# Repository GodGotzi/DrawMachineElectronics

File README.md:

# DrawMachineElectronics
DrawMachineElectronics

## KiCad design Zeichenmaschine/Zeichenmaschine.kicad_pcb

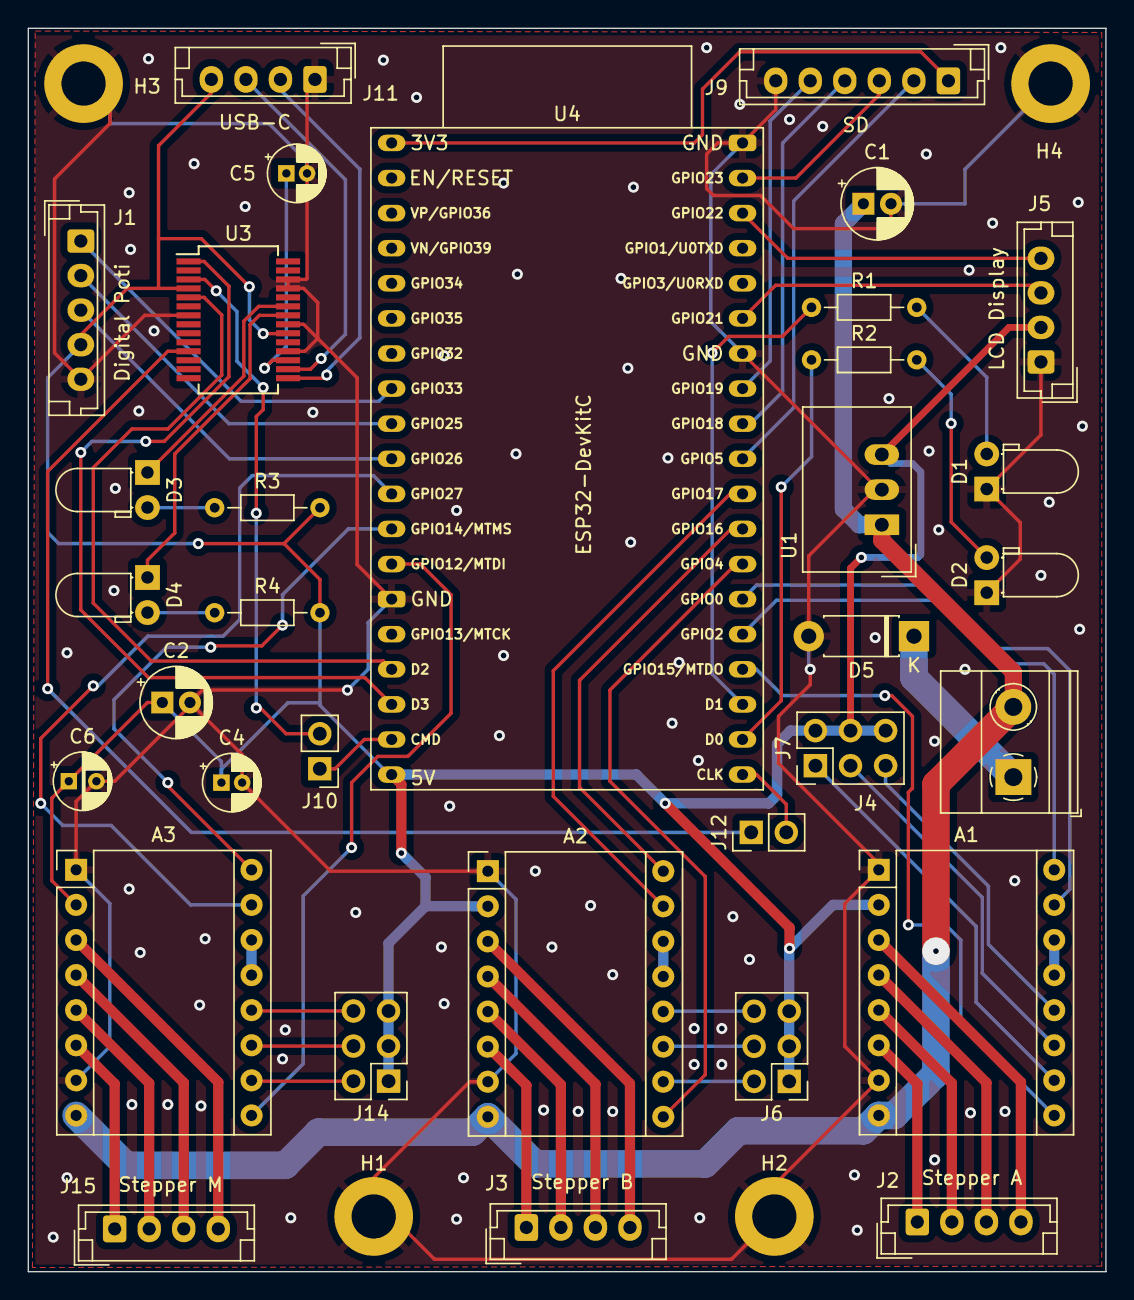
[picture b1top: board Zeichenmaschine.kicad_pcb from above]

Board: 2 copper layers, 78.0 x 90.0 mm, 37 parts (0 on the bottom side), 64 nets.

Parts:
A1: Stepper_1_A4988; Pololu_Breakout-16_15.2x20.3mm
A2: Stepper_2_A4988; Pololu_Breakout-16_15.2x20.3mm
A3: Stepper_3_A4988; Pololu_Breakout-16_15.2x20.3mm
C1, C2: C_Polarized; CP_Radial_D5.0mm_P2.00mm
C4, C5: 0.1µF; CP_Radial_D4.0mm_P1.50mm
C6: 10µF; CP_Radial_D4.0mm_P2.00mm
D1, D2: RED; LED_D3.0mm_Horizontal_O1.27mm_Z2.0mm
D3: RED_USB; LED_D3.0mm_Horizontal_O1.27mm_Z2.0mm
D4: GREEN_USB; LED_D3.0mm_Horizontal_O1.27mm_Z2.0mm
D5: D_Schottky; D_DO-41_SOD81_P7.62mm_Horizontal
H1, H2, H3, H4: MountingHole_Pad; MountingHole_3.2mm_M3_ISO7380_Pad
J1: interface; JST_EH_B5B-EH-A_1x05_P2.50mm_Vertical
J2: Stepper_1; JST_EH_B4B-EH-A_1x04_P2.50mm_Vertical
J3: Stepper_2; JST_EH_B4B-EH-A_1x04_P2.50mm_Vertical
J4: Screw_Terminal_01x02; TerminalBlock_Phoenix_MKDS-1,5-2-5.08_1x02_P5.08mm_Horizont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
J5: Display; JST_EH_B4B-EH-A_1x04_P2.50mm_Vertical
J6: Stepper_2_JUMPER; PinHeader_2x03_P2.54mm_Vertical
J7: Stepper_1_JUMPER; PinHeader_2x03_P2.54mm_Vertical
J9: SD_SPI; JST_EH_B6B-EH-A_1x06_P2.50mm_Vertical
J10, J12: Conn_01x02_Male; PinHeader_1x02_P2.54mm_Vertical
J11: USB_C; JST_EH_B4B-EH-A_1x04_P2.50mm_Vertical
J14: Stepper_3_JUMPER; PinHeader_2x03_P2.54mm_Vertical
J15: Stepper_3; JST_EH_B4B-EH-A_1x04_P2.50mm_Vertical
R1, R2: 270; R_Axial_DIN0204_L3.6mm_D1.6mm_P7.62mm_Horizontal
R3, R4: 1k; R_Axial_DIN0204_L3.6mm_D1.6mm_P7.62mm_Horizontal
U1: TSR_1-2450; Converter_DCDC_TRACO_TSR-1_THT
U3: FT232RL; SSOP-28_5.3x10.2mm_P0.65mm
U4: ESP32-DevKitC

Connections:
+3V3: J9.1, U4.1 (3V3)
+5V: A1.2 (VDD), A2.2 (VDD), A3.2 (VDD), C2.1, C4.1, C6.1, J1.4, J5.2, J6.1, J6.3, J6.5, J7.2, J7.4, J7.6, J11.4, J14.1, J14.3, J14.5, R3.2, R4.2, U1.3 (Vout), U3.4 (VCCIO), U3.20 (VCC), U4.19 (5V)
+12V: A1.8 (VMOT), A2.8 (VMOT), A3.8 (VMOT), C1.1, J4.2, U1.1 (Vin)
/CLK: J9.4, U4.30 (GPIO18)
/CS: J9.2, U4.29 (*GPIO5)
/CTS: J12.1, U3.11 (CTS)
/LED1: R1.1, U4.22 (SD_DATA1/GPIO8)
/LED2: R2.1, U4.21 (SD_DATA0/GPIO7)
/MISO: J9.5, U4.31 (GPIO19)
/MOSI: J9.3, U4.37 (GPIO23)
/RTS: J10.2, U3.3 (RTS)
/RX: U3.5 (RXD), U4.16 (SD_DATA2/GPIO9)
/Stepper_1_DIR: A3.16 (DIR), U4.12 (MTMS/GPIO14/ADC2_CH6)
/Stepper_1_STEP: A3.15 (STEP), U4.11 (ADC2_CH7/GPIO27)
/Stepper_2_DIR: A2.16 (DIR), U4.27 (GPIO16)
/Stepper_2_STEP: A2.15 (STEP), U4.28 (GPIO17)
/TX: U3.1 (TXD), U4.17 (SD_DATA3/GPIO10)
/display_SCL: J5.4, U4.36 (GPIO22)
/display_SDA: J5.3, U4.33 (GPIO21)
/enable_Stepper_1: A3.9 (~ENABLE), U4.13 (*MTDI/GPIO12/ADC2_CH5)
/enable_Stepper_2: A2.9 (~ENABLE), U4.26 (ADC2_CH0/GPIO4)
/enable_stepper_gear_motor: A1.9 (~ENABLE), U4.23 (*MTDO/GPIO15/ADC2_CH3)
/interface_CLK: J1.1, U4.8 (32K_XN/GPIO33/ADC1_CH5)
/interface_DT: J1.2, U4.9 (DAC_1/ADC2_CH8/GPIO25)
/interface_SW: J1.3, U4.10 (DAC_2/ADC2_CH9/GPIO26)
/stepper_gear_motor_1A: A1.15 (STEP), U4.25 (*GPIO0/BOOT/ADC2_CH1)
/stepper_gear_motor_2A: A1.16 (DIR), U4.24 (ADC2_CH2/*GPIO2)
GND: A1.1 (GND), A1.7 (GND), A2.1 (GND), A2.7 (GND), A3.1 (GND), A3.7 (GND), C1.2, C2.2, C4.2, C5.2, C6.2, D1.1 (K), D2.1 (K), D5.2 (A), H1.1, H2.1, H3.1, H4.1, J1.5, J5.1, J9.6, J11.1, U1.2 (GND), U3.7 (GND), U3.18 (GND), U3.21 (GND), U3.25 (AGND), U3.26 (TEST), U4.14 (GND), U4.32 (GND), U4.38 (GND)
unnamed: A1.3 (1B), J2.4
unnamed: A1.4 (1A), J2.3
unnamed: A1.5 (2A), J2.2
unnamed: A1.6 (2B), J2.1
unnamed: A1.10 (MS1), J7.1
unnamed: A1.11 (MS2), J7.3
unnamed: A1.12 (MS3), J7.5
unnamed: A1.13 (~RESET), A1.14 (~SLEEP)
unnamed: A2.3 (1B), J3.4
unnamed: A2.4 (1A), J3.3
unnamed: A2.5 (2A), J3.2
unnamed: A2.6 (2B), J3.1
unnamed: A2.10 (MS1), J6.2
unnamed: A2.11 (MS2), J6.4
unnamed: A2.12 (MS3), J6.6
unnamed: A2.13 (~RESET), A2.14 (~SLEEP)
unnamed: A3.3 (1B), J15.4
unnamed: A3.4 (1A), J15.3
unnamed: A3.5 (2A), J15.2
unnamed: A3.6 (2B), J15.1
unnamed: A3.10 (MS1), J14.2
unnamed: A3.11 (MS2), J14.4
unnamed: A3.12 (MS3), J14.6
unnamed: A3.13 (~RESET), A3.14 (~SLEEP)
unnamed: C5.1, U3.17 (3V3OUT)
unnamed: D1.2 (A), R1.2
unnamed: D2.2 (A), R2.2
unnamed: D3.1 (K), U3.23 (CBUS0)
unnamed: D3.2 (A), R3.1
unnamed: D4.1 (K), U3.22 (CBUS1)
unnamed: D4.2 (A), R4.1
unnamed: D5.1 (K), J4.1
unnamed: J10.1, U4.18 (CMD)
unnamed: J11.2, U3.15 (USBD+)
unnamed: J11.3, U3.16 (USBD-)
unnamed: J12.2, U4.20 (SD_CLK/GPIO6)

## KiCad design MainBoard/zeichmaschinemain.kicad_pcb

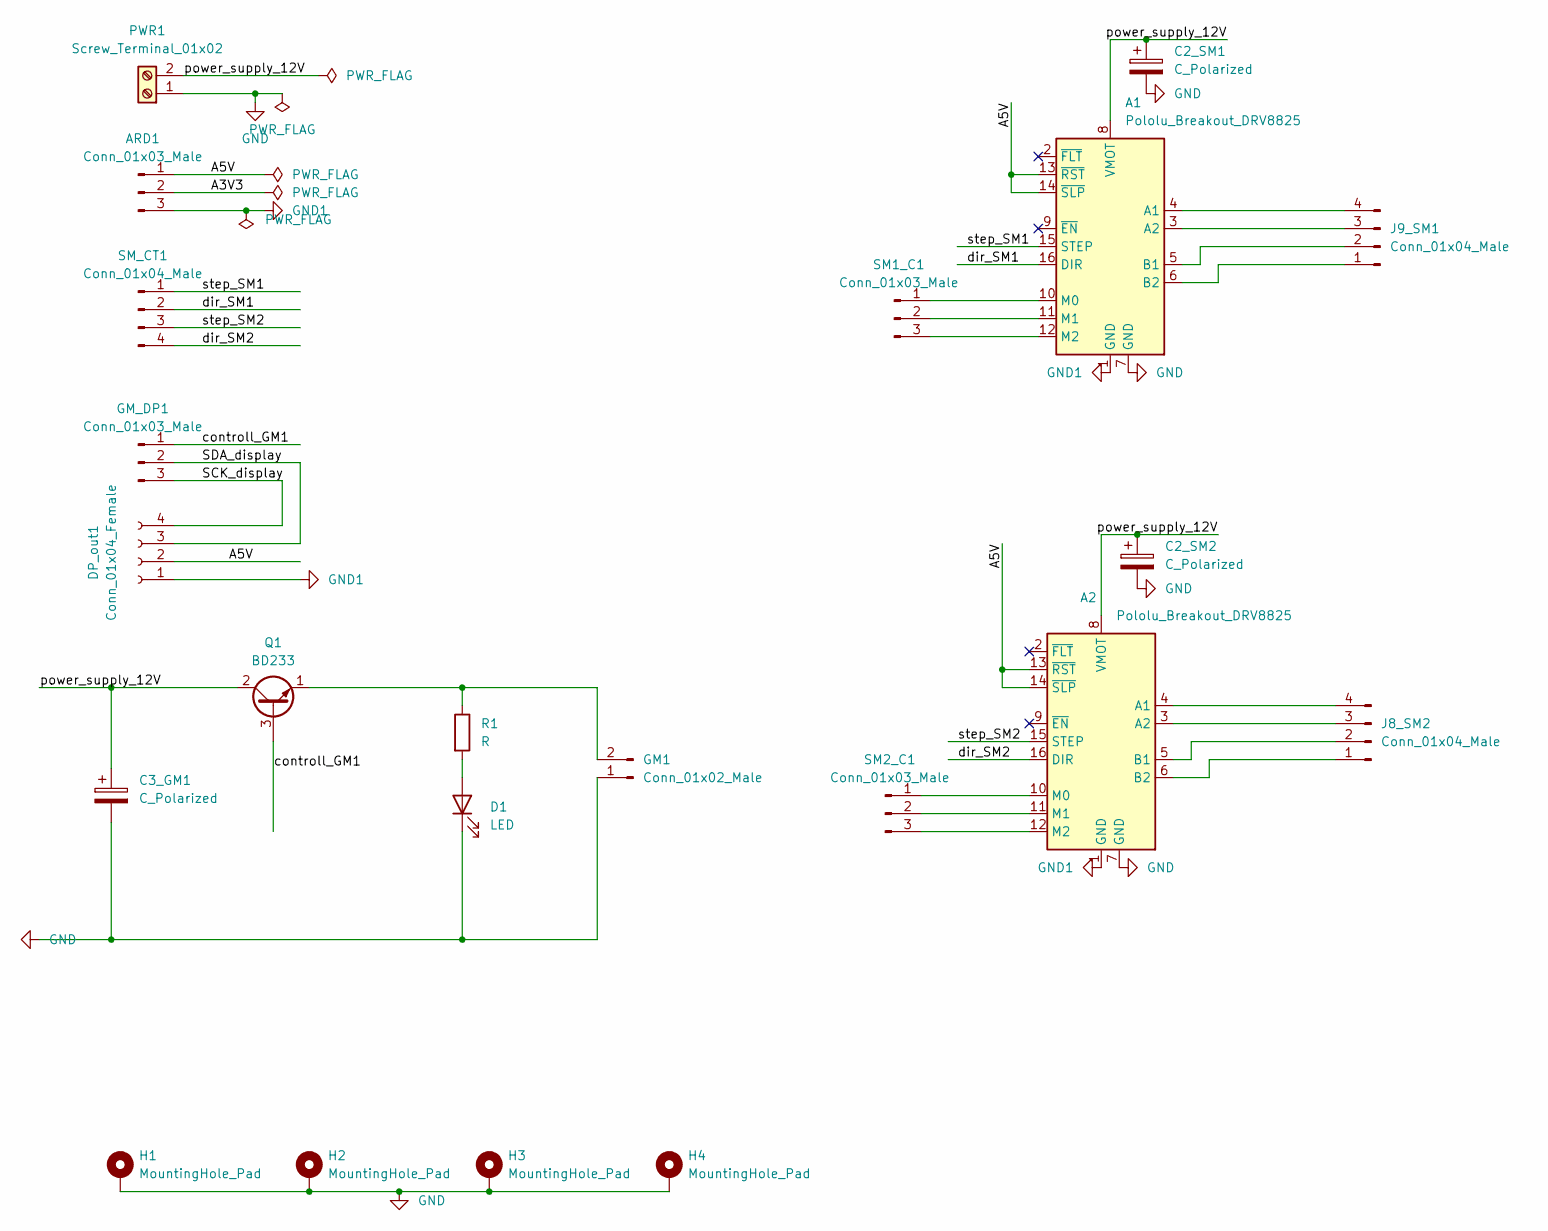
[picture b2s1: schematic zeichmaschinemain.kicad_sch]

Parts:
A1, A2: Pololu_Breakout_DRV8825; Pololu_Breakout-16_15.2x20.3mm
ARD1: Conn_01x03_Male; PinHeader_1x03_P2.54mm_Horizontal
C2_SM1, C2_SM2, C3_GM1: C_Polarized; CP_Radial_D5.0mm_P2.00mm
D1: LED; LED_D5.0mm
DP_out1: Conn_01x04_Female; PinSocket_1x04_P2.54mm_Horizontal
GM1: Conn_01x02_Male; PinHeader_1x02_P2.54mm_Horizontal
GM_DP1: Conn_01x03_Male; PinHeader_1x03_P2.54mm_Horizontal
H1, H2, H3, H4: MountingHole_Pad; MountingHole_3.2mm_M3_Pad
J8_SM2, J9_SM1: Conn_01x04_Male; PinHeader_1x04_P2.54mm_Horizontal
PWR1: Screw_Terminal_01x02; TerminalBlock_bornier-2_P5.08mm
Q1: BD233; TO-126-3_Vertical
R1: R; R_Axial_DIN0204_L3.6mm_D1.6mm_P1.90mm_Vertical
SM1_C1, SM2_C1: Conn_01x03_Male; PinHeader_1x03_P2.54mm_Vertical
SM_CT1: Conn_01x04_Male; PinHeader_1x04_P2.54mm_Horizontal

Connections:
/A3V3: ARD1.2
/A5V: A1.13 (~RST), A1.14 (~SLP), A2.13 (~RST), A2.14 (~SLP), ARD1.1, DP_out1.2
/SCK_display: DP_out1.4, GM_DP1.3
/SDA_display: DP_out1.3, GM_DP1.2
/controll_GM1: GM_DP1.1, Q1.3 (B)
/dir_SM1: A1.16 (DIR), SM_CT1.2
/dir_SM2: A2.16 (DIR), SM_CT1.4
/power_supply_12V: A1.8 (VMOT), A2.8 (VMOT), C2_SM1.1, C2_SM2.1, C3_GM1.1, PWR1.2, Q1.2 (C)
/step_SM1: A1.15 (STEP), SM_CT1.1
/step_SM2: A2.15 (STEP), SM_CT1.3
GND: A1.7 (GND), A2.7 (GND), C2_SM1.2, C2_SM2.2, C3_GM1.2, D1.1 (K), GM1.1, H1.1, H2.1, H3.1, H4.1, PWR1.1
GND1: A1.1 (GND), A2.1 (GND), ARD1.3, DP_out1.1
unnamed: A1.3 (A2), J9_SM1.3
unnamed: A1.4 (A1), J9_SM1.4
unnamed: A1.5 (B1), J9_SM1.2
unnamed: A1.6 (B2), J9_SM1.1
unnamed: A1.10 (M0), SM1_C1.1
unnamed: A1.11 (M1), SM1_C1.2
unnamed: A1.12 (M2), SM1_C1.3
unnamed: A2.3 (A2), J8_SM2.3
unnamed: A2.4 (A1), J8_SM2.4
unnamed: A2.5 (B1), J8_SM2.2
unnamed: A2.6 (B2), J8_SM2.1
unnamed: A2.10 (M0), SM2_C1.1
unnamed: A2.11 (M1), SM2_C1.2
unnamed: A2.12 (M2), SM2_C1.3
unnamed: D1.2 (A), R1.2
unnamed: GM1.2, Q1.1 (E), R1.1

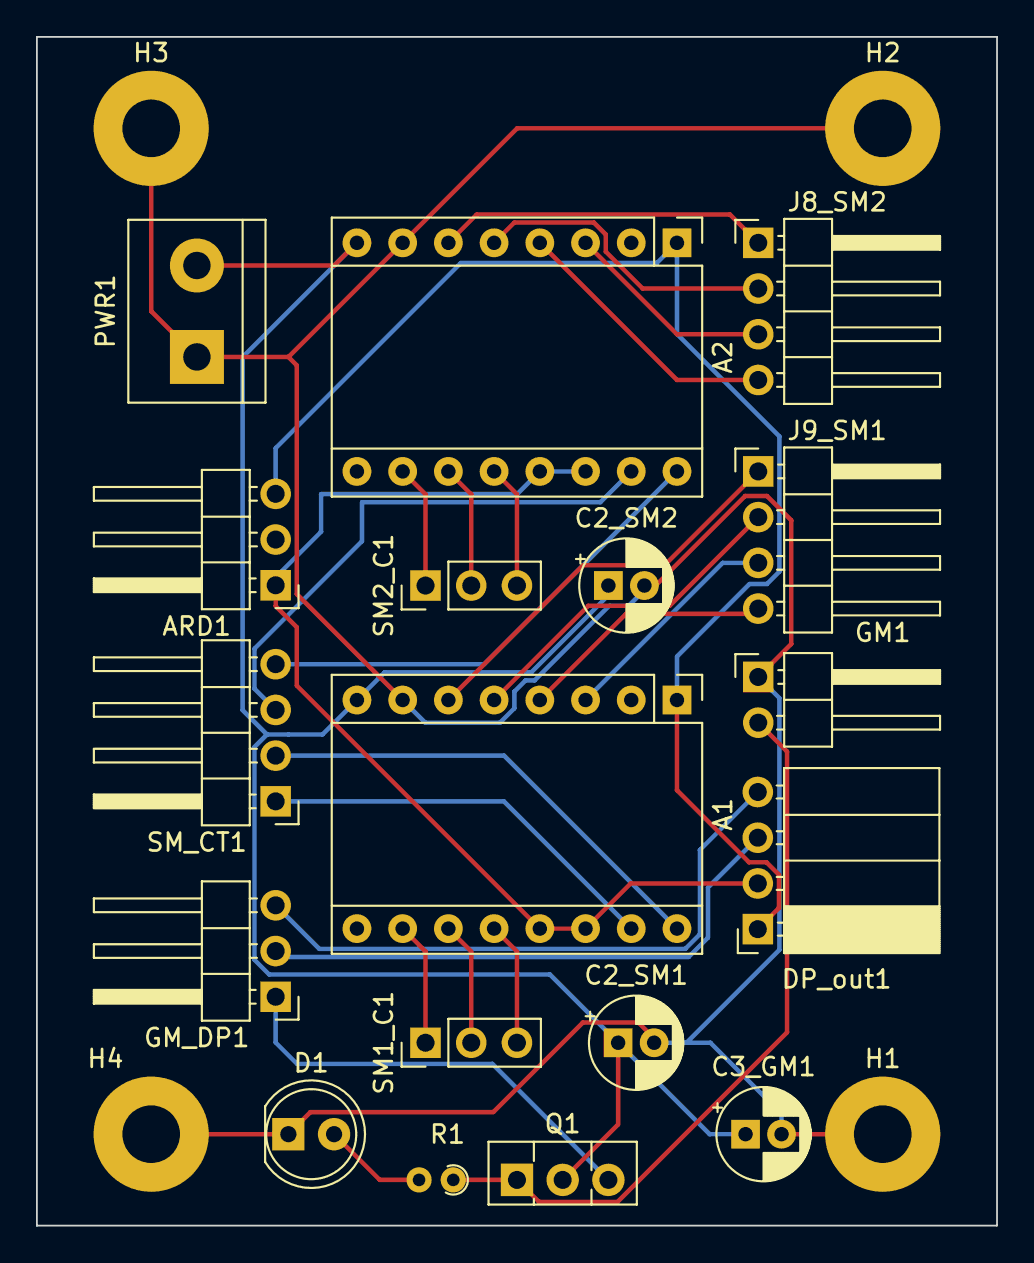
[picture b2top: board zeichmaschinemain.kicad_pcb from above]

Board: 2 copper layers, 53.3 x 66.0 mm, 22 parts (0 on the bottom side), 27 nets.

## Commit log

2022-06-04 Adding MainBoard
2022-11-08 nice
2022-12-24 test
2022-12-24 test2
2022-12-25 asjhgdnsa
2023-04-16 DrawMachine PCB V1
